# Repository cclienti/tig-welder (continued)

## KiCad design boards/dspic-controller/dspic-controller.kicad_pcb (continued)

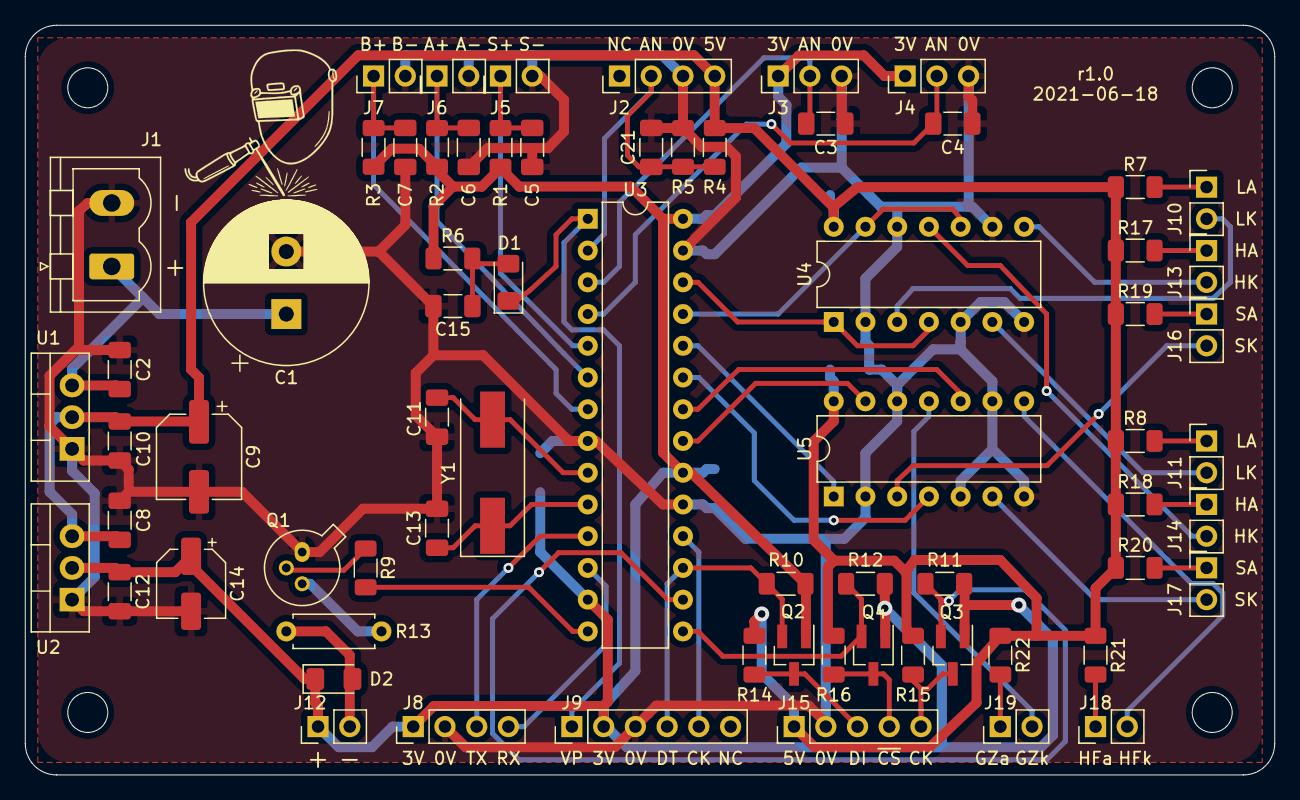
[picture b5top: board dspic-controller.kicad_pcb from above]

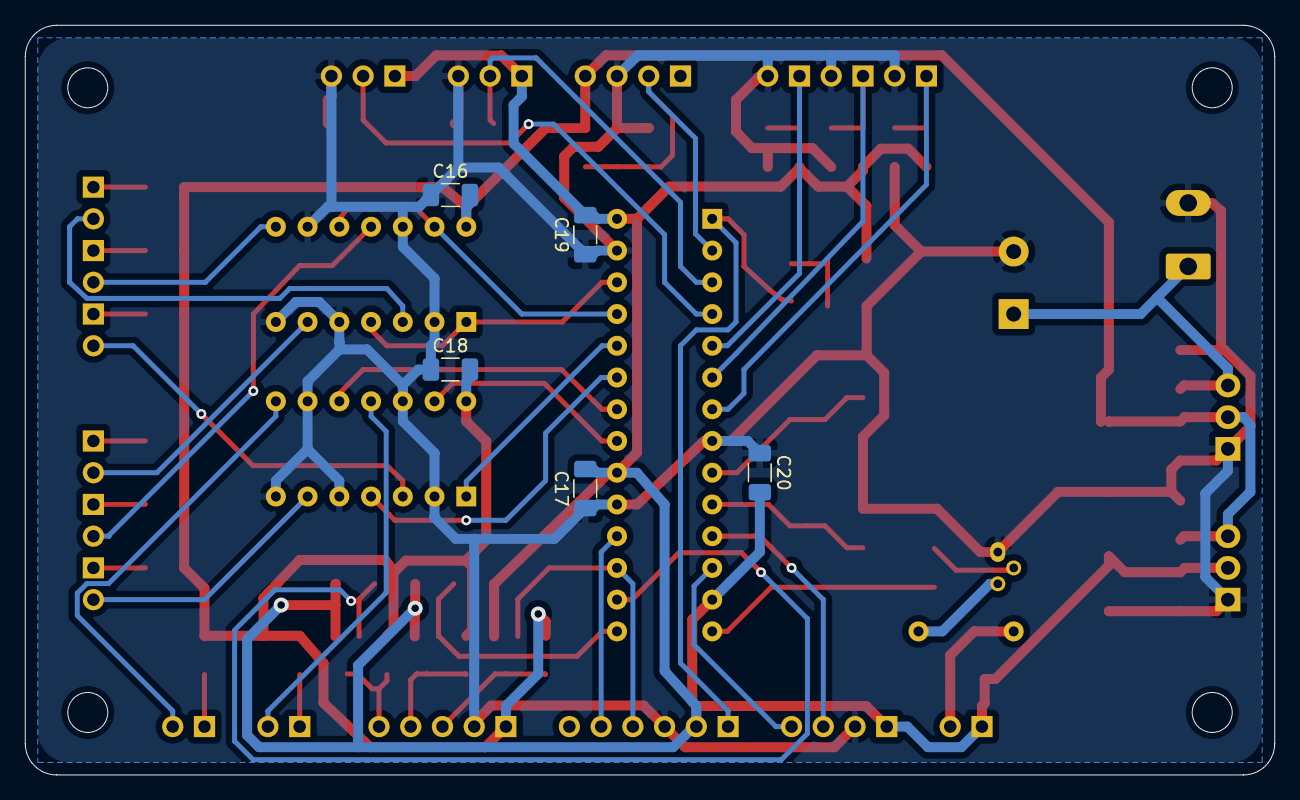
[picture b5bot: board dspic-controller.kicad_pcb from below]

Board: 2 copper layers, 100.0 x 60.0 mm, 78 parts (5 on the bottom side), 49 nets.

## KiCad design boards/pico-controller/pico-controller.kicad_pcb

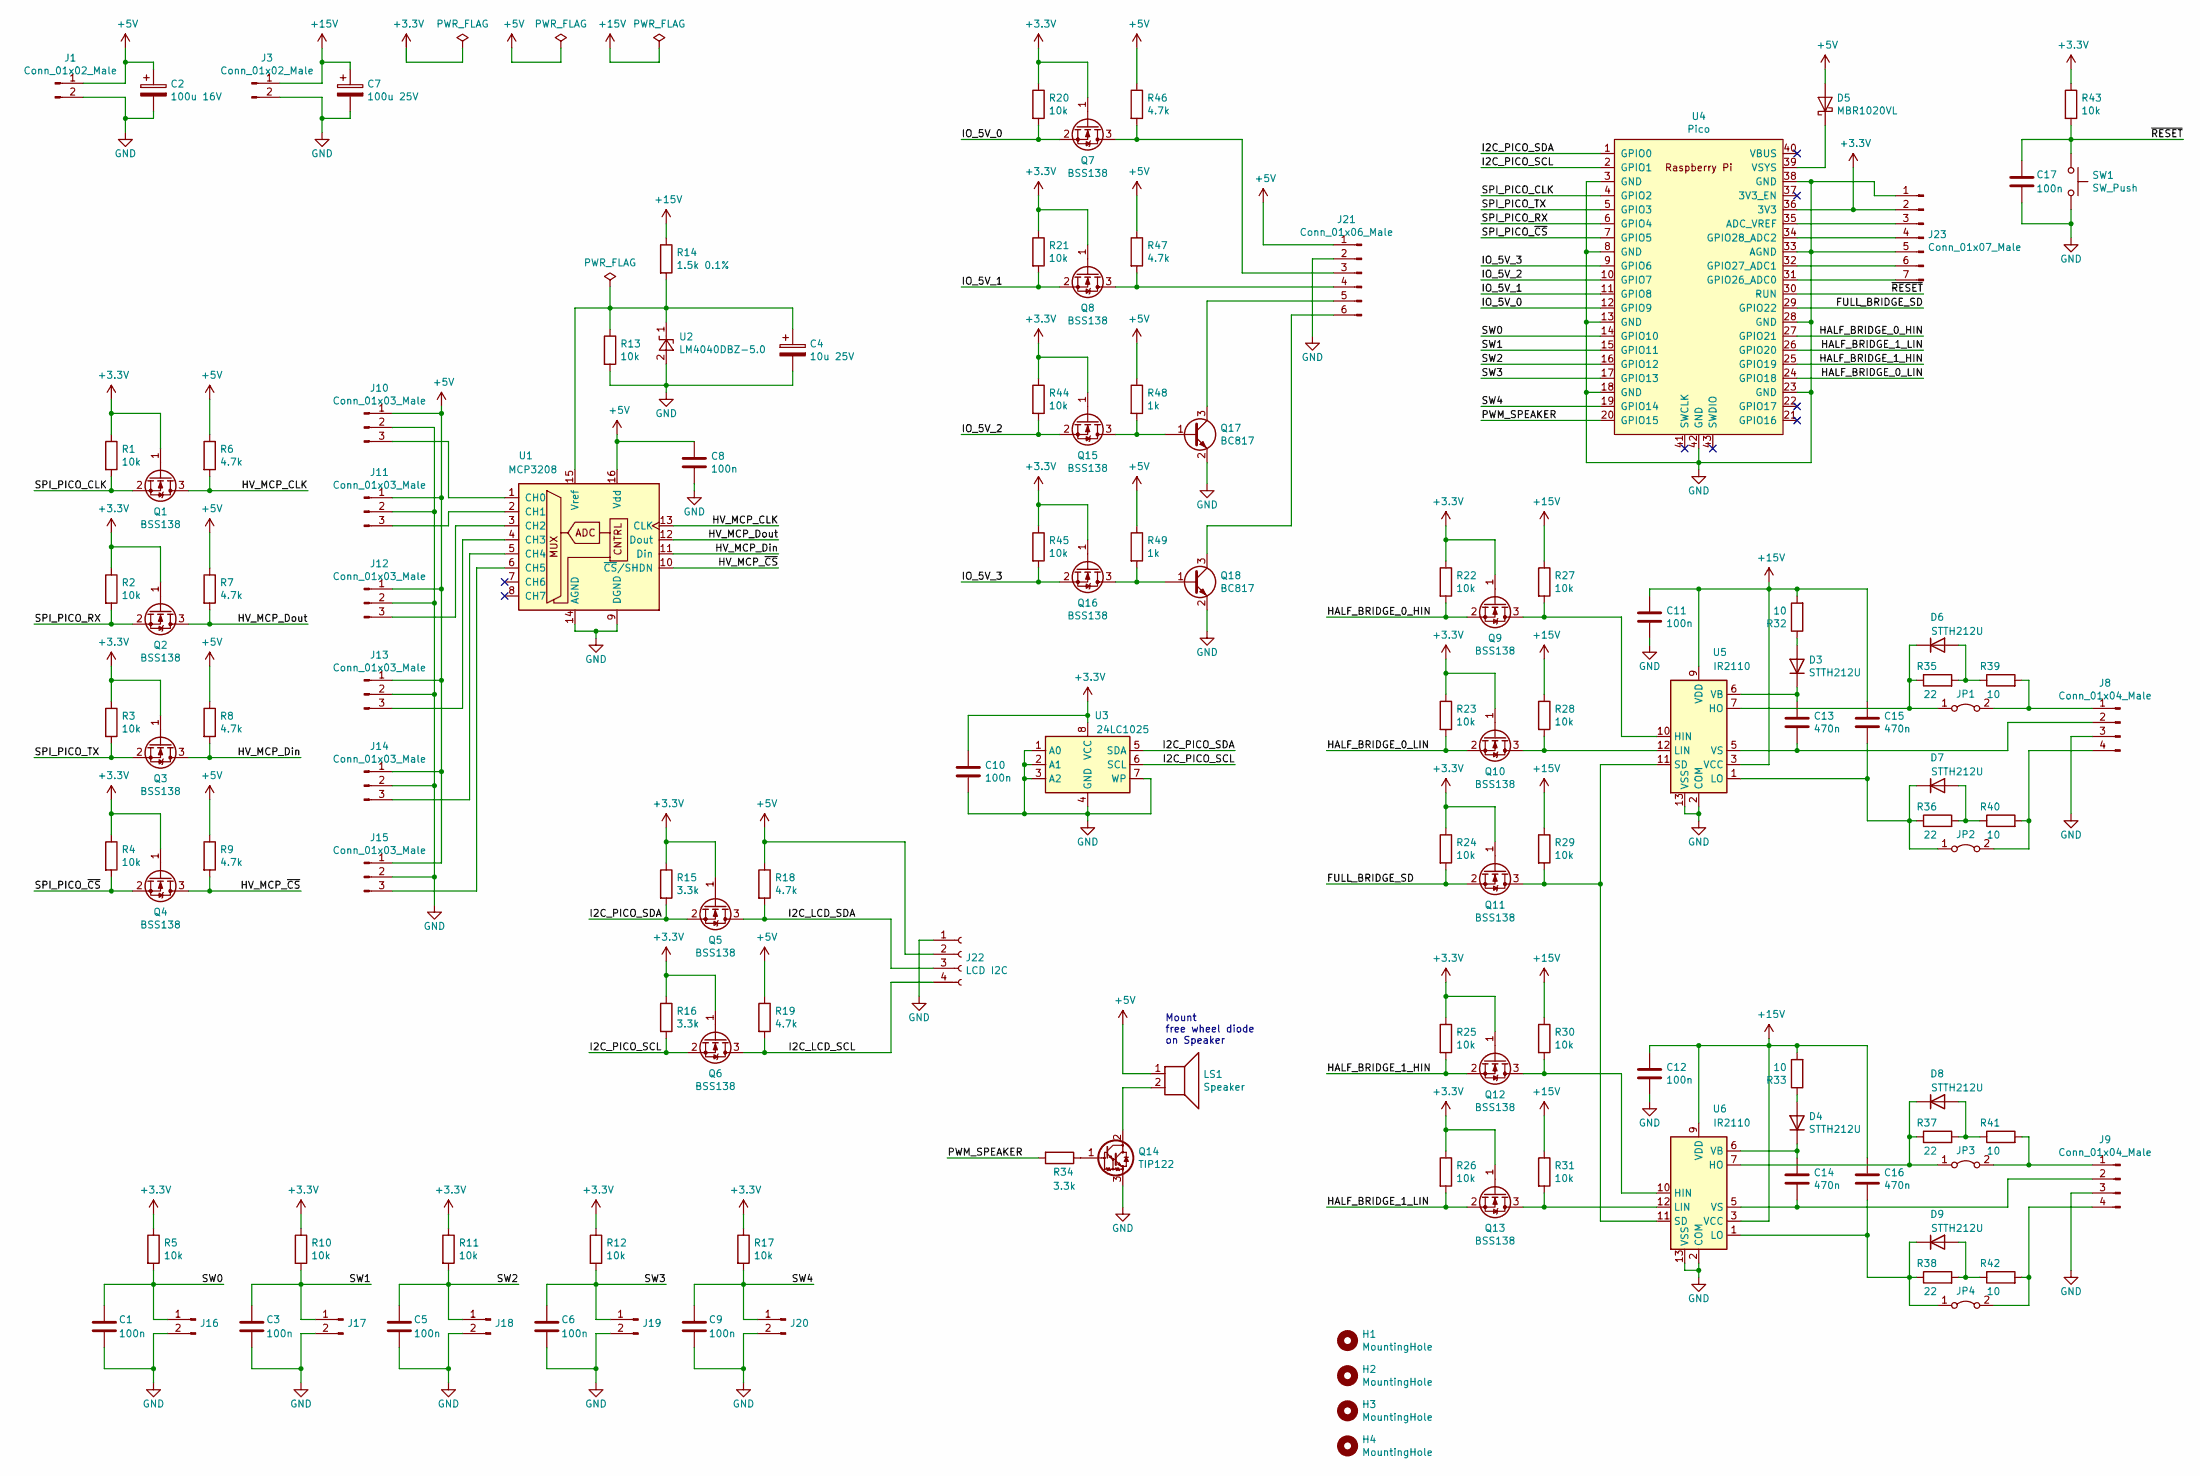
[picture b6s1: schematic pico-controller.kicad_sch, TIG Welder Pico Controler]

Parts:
C1, C3, C5, C6, C8, C9, C10, C11, C12, C17: 100n; C_1206_3216Metric_Pad1.33x1.80mm_HandSolder
C2: 100u 16V; CP_Elec_6.3x5.4
C4: 10u 25V; CP_Elec_5x5.3
C7: 100u 25V; CP_Elec_6.3x7.7
C13, C14, C15, C16: 470n; C_Rect_L13.0mm_W6.0mm_P10.00mm_FKS3_FKP3_MKS4
D3, D4, D6, D7, D8, D9: STTH212U; D_SMB
D5: MBR1020VL; D_SMA
H1, H2, H3, H4: MountingHole; MountingHole_3mm
J1, J3: Conn_01x02_Male; PhoenixContact_MSTBVA_2,5_2-G-5,08_1x02_P5.08mm_Vertical
J8, J9: Conn_01x04_Male; PinHeader_1x04_P2.54mm_Vertical
J10, J11, J12, J13, J14, J15: Conn_01x03_Male; PinHeader_1x03_P2.54mm_Vertical
J16, J17, J18, J19, J20: Conn_01x02_Male; PinHeader_1x02_P2.54mm_Vertical
J21: Conn_01x06_Male; PinHeader_1x06_P2.54mm_Vertical
J22: LCD I2C; PinHeader_1x04_P2.54mm_Vertical
J23: Conn_01x07_Male; PinHeader_1x07_P2.54mm_Vertical
JP1, JP2, JP3, JP4: Jumper_2_Bridged; PinHeader_1x02_P2.54mm_Vertical
LS1: Speaker; PinHeader_1x02_P2.54mm_Vertical
Q1, Q2, Q3, Q4, Q5, Q6, Q7, Q8, Q9, Q10, Q11, Q12, Q13, Q15, Q16: BSS138; SOT-23_Handsoldering
Q14: TIP122; TO-220-3_Horizontal_TabDown
Q17, Q18: BC817; SOT-23
R1, R2, R3, R4, R5, R10, R11, R12, R13, R17, R20, R21, R22, R23, R24, R25, R26, R27, R28, R29, R30, R31, R43, R44, R45: 10k; R_1206_3216Metric_Pad1.30x1.75mm_HandSolder
R6, R7, R8, R9, R18, R19, R46, R47: 4.7k; R_1206_3216Metric_Pad1.30x1.75mm_HandSolder
R14: 1.5k 0.1%; R_1206_3216Metric_Pad1.30x1.75mm_HandSolder
R15, R16, R34: 3.3k; R_1206_3216Metric_Pad1.30x1.75mm_HandSolder
R32, R33, R39, R40, R41, R42: 10; R_1206_3216Metric_Pad1.30x1.75mm_HandSolder
R35, R36, R37, R38: 22; R_1206_3216Metric_Pad1.30x1.75mm_HandSolder
R48, R49: 1k; R_1206_3216Metric_Pad1.30x1.75mm_HandSolder
SW1: SW_Push; SW_PUSH_6mm_H5mm
U1: MCP3208; DIP-16_W7.62mm
U2: LM4040DBZ-5.0; SOT-23_Handsoldering
U3: 24LC1025; DIP-8_W7.62mm
U4: Pico; RPi_Pico_SMD_TH
U5, U6: IR2110; DIP-14_W7.62mm

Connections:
+3V3: C10.1, J23.2, Q1.1 (G), Q2.1 (G), Q3.1 (G), Q4.1 (G), Q5.1 (G), Q6.1 (G), Q7.1 (G), Q8.1 (G), Q9.1 (G), Q10.1 (G), Q11.1 (G), Q12.1 (G), Q13.1 (G), Q15.1 (G), Q16.1 (G), R1.1, R2.1, R3.1, R4.1, R5.1, R10.1, R11.1, R12.1, R15.1, R16.1, R17.1, R20.1, R21.1, R22.1, R23.1, R24.1, R25.1, R26.1, R43.1, R44.1, R45.1, U3.8 (VCC), U4.36 (3V3)
+5V: C2.1, C8.1, D5.2 (A), J1.1, J10.1, J11.1, J12.1, J13.1, J14.1, J15.1, J21.1, J22.2, LS1.1, R6.1, R7.1, R8.1, R9.1, R18.1, R19.1, R46.1, R47.1, R48.1, R49.1, U1.16 (Vdd)
+15V: C7.1, C11.1, C12.1, C15.1, C16.1, J3.1, R14.1, R27.1, R28.1, R29.1, R30.1, R31.1, R32.2, R33.2, U5.3 (VCC), U5.9 (VDD), U6.3 (VCC), U6.9 (VDD)
/FULL_BRIDGE_SD: Q11.2 (S), R24.2, U4.29 (GPIO22)
/HALF_BRIDGE_0_HIN: Q9.2 (S), R22.2, U4.27 (GPIO21)
/HALF_BRIDGE_0_LIN: Q10.2 (S), R23.2, U4.24 (GPIO18)
/HALF_BRIDGE_1_HIN: Q12.2 (S), R25.2, U4.25 (GPIO19)
/HALF_BRIDGE_1_LIN: Q13.2 (S), R26.2, U4.26 (GPIO20)
/HV_MCP_CLK: Q1.3 (D), R6.2, U1.13 (CLK)
/HV_MCP_Din: Q3.3 (D), R8.2, U1.11 (Din)
/HV_MCP_Dout: Q2.3 (D), R7.2, U1.12 (Dout)
/HV_MCP_~CS: Q4.3 (D), R9.2, U1.10 (~CS/SHDN)
/I2C_LCD_SCL: J22.4, Q6.3 (D), R19.2
/I2C_LCD_SDA: J22.3, Q5.3 (D), R18.2
/I2C_PICO_SCL: Q6.2 (S), R16.2, U3.6 (SCL), U4.2 (GPIO1)
/I2C_PICO_SDA: Q5.2 (S), R15.2, U3.5 (SDA), U4.1 (GPIO0)
/IO_5V_0: Q7.2 (S), R20.2, U4.12 (GPIO9)
/IO_5V_1: Q8.2 (S), R21.2, U4.11 (GPIO8)
/IO_5V_2: Q15.2 (S), R44.2, U4.10 (GPIO7)
/IO_5V_3: Q16.2 (S), R45.2, U4.9 (GPIO6)
/PWM_SPEAKER: R34.2, U4.20 (GPIO15)
/SPI_PICO_CLK: Q1.2 (S), R1.2, U4.4 (GPIO2)
/SPI_PICO_RX: Q2.2 (S), R2.2, U4.6 (GPIO4)
/SPI_PICO_TX: Q3.2 (S), R3.2, U4.5 (GPIO3)
/SPI_PICO_~CS: Q4.2 (S), R4.2, U4.7 (GPIO5)
/SW0: C1.1, J16.1, R5.2, U4.14 (GPIO10)
/SW1: C3.1, J17.1, R10.2, U4.15 (GPIO11)
/SW2: C5.1, J18.1, R11.2, U4.16 (GPIO12)
/SW3: C6.1, J19.1, R12.2, U4.17 (GPIO13)
/SW4: C9.1, J20.1, R17.2, U4.19 (GPIO14)
/~RESET: C17.1, R43.2, SW1.1, U4.30 (RUN)
GND: C1.2, C2.2, C3.2, C4.2, C5.2, C6.2, C7.2, C8.2, C9.2, C10.2, C11.2, C12.2, C17.2, J1.2, J3.2, J8.3, J9.3, J10.2, J11.2, J12.2, J13.2, J14.2, J15.2, J16.2, J17.2, J18.2, J19.2, J20.2, J21.2, J22.1, J23.1, J23.5, Q14.3 (E), Q17.2 (E), Q18.2 (E), R13.2, SW1.2, U1.9 (DGND), U1.14 (AGND), U2.2 (A), U3.1 (A0), U3.2 (A1), U3.3 (A2), U3.4 (GND), U3.7 (WP), U4.3 (GND), U4.8 (GND), U4.13 (GND), U4.18 (GND), U4.23 (GND), U4.28 (GND), U4.33 (AGND), U4.38 (GND), U4.42 (GND), U5.2 (COM), U5.13 (VSS), U6.2 (COM), U6.13 (VSS)
unnamed: C4.1, R13.1, R14.2, U1.15 (Vref), U2.1 (K)
unnamed: C13.1, D3.1 (K), U5.6 (VB)
unnamed: C13.2, J8.2, U5.5 (VS)
unnamed: C14.1, D4.1 (K), U6.6 (VB)
unnamed: C14.2, J9.2, U6.5 (VS)
unnamed: C15.2, D7.1 (K), JP2.1 (A), R36.1, U5.1 (LO)
unnamed: C16.2, D9.1 (K), JP4.1 (A), R38.1, U6.1 (LO)
unnamed: D3.2 (A), R32.1
unnamed: D4.2 (A), R33.1
unnamed: D5.1 (K), U4.39 (VSYS)
unnamed: D6.1 (K), JP1.1 (A), R35.1, U5.7 (HO)
unnamed: D6.2 (A), R35.2, R39.1
unnamed: D7.2 (A), R36.2, R40.1
unnamed: D8.1 (K), JP3.1 (A), R37.1, U6.7 (HO)
unnamed: D8.2 (A), R37.2, R41.1
unnamed: D9.2 (A), R38.2, R42.1
unnamed: J8.1, JP1.2 (B), R39.2
unnamed: J8.4, JP2.2 (B), R40.2
unnamed: J9.1, JP3.2 (B), R41.2
unnamed: J9.4, JP4.2 (B), R42.2
unnamed: J10.3, U1.1 (CH0)
unnamed: J11.3, U1.2 (CH1)
unnamed: J12.3, U1.3 (CH2)
unnamed: J13.3, U1.4 (CH3)
unnamed: J14.3, U1.5 (CH4)
unnamed: J15.3, U1.6 (CH5)
unnamed: J21.3, Q7.3 (D), R46.2
unnamed: J21.4, Q8.3 (D), R47.2
unnamed: J21.5, Q17.3 (C)
unnamed: J21.6, Q18.3 (C)
unnamed: J23.3, U4.35 (ADC_VREF)
unnamed: J23.4, U4.34 (GPIO28_ADC2)
unnamed: J23.6, U4.32 (GPIO27_ADC1)
unnamed: J23.7, U4.31 (GPIO26_ADC0)
unnamed: LS1.2, Q14.2 (C)
unnamed: Q9.3 (D), R27.2, U5.10 (HIN)
unnamed: Q10.3 (D), R28.2, U5.12 (LIN)
unnamed: Q11.3 (D), R29.2, U5.11 (SD), U6.11 (SD)
unnamed: Q12.3 (D), R30.2, U6.10 (HIN)
unnamed: Q13.3 (D), R31.2, U6.12 (LIN)
unnamed: Q14.1 (B), R34.1
unnamed: Q15.3 (D), Q17.1 (B), R48.2
unnamed: Q16.3 (D), Q18.1 (B), R49.2

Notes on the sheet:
Mount free wheel diode on Speaker

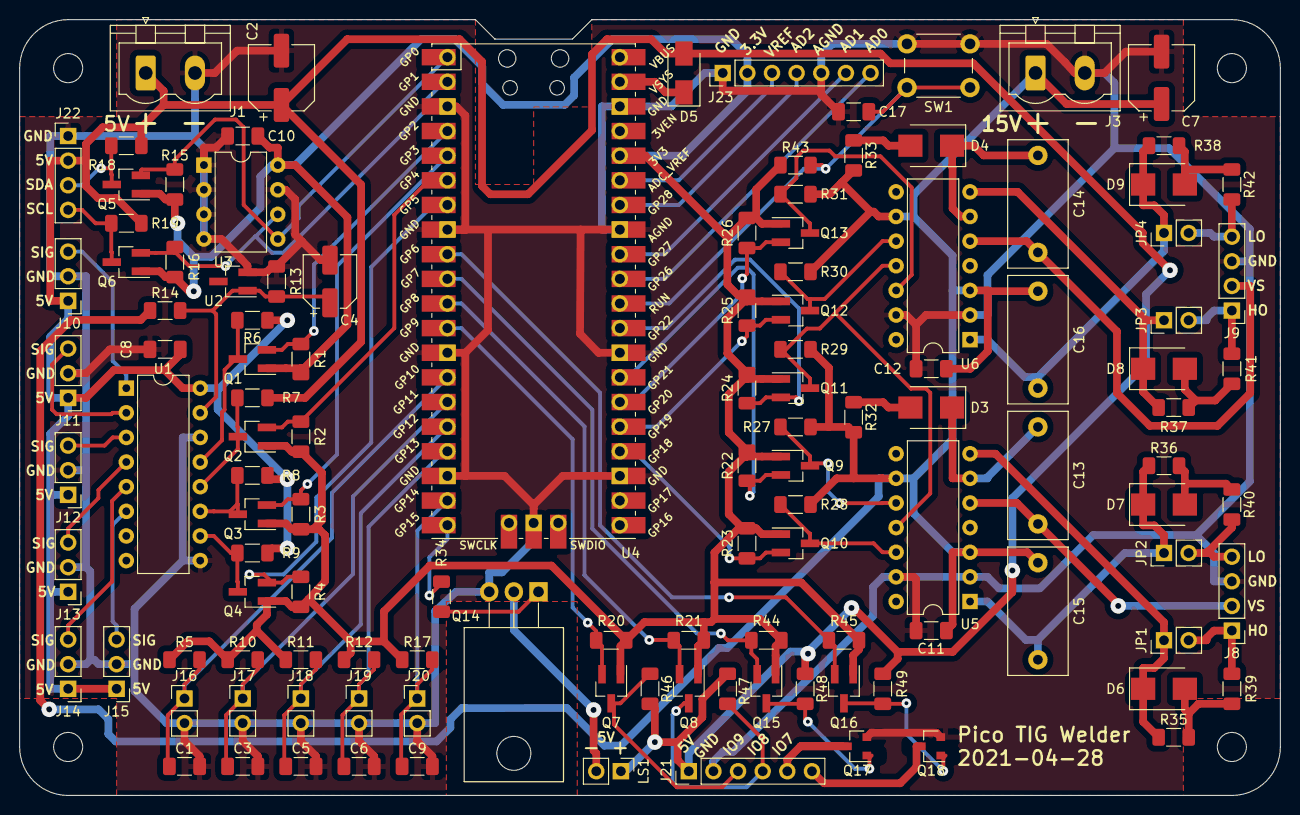
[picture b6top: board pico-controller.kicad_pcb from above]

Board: 2 copper layers, 130.0 x 80.0 mm, 125 parts (0 on the bottom side), 75 nets.

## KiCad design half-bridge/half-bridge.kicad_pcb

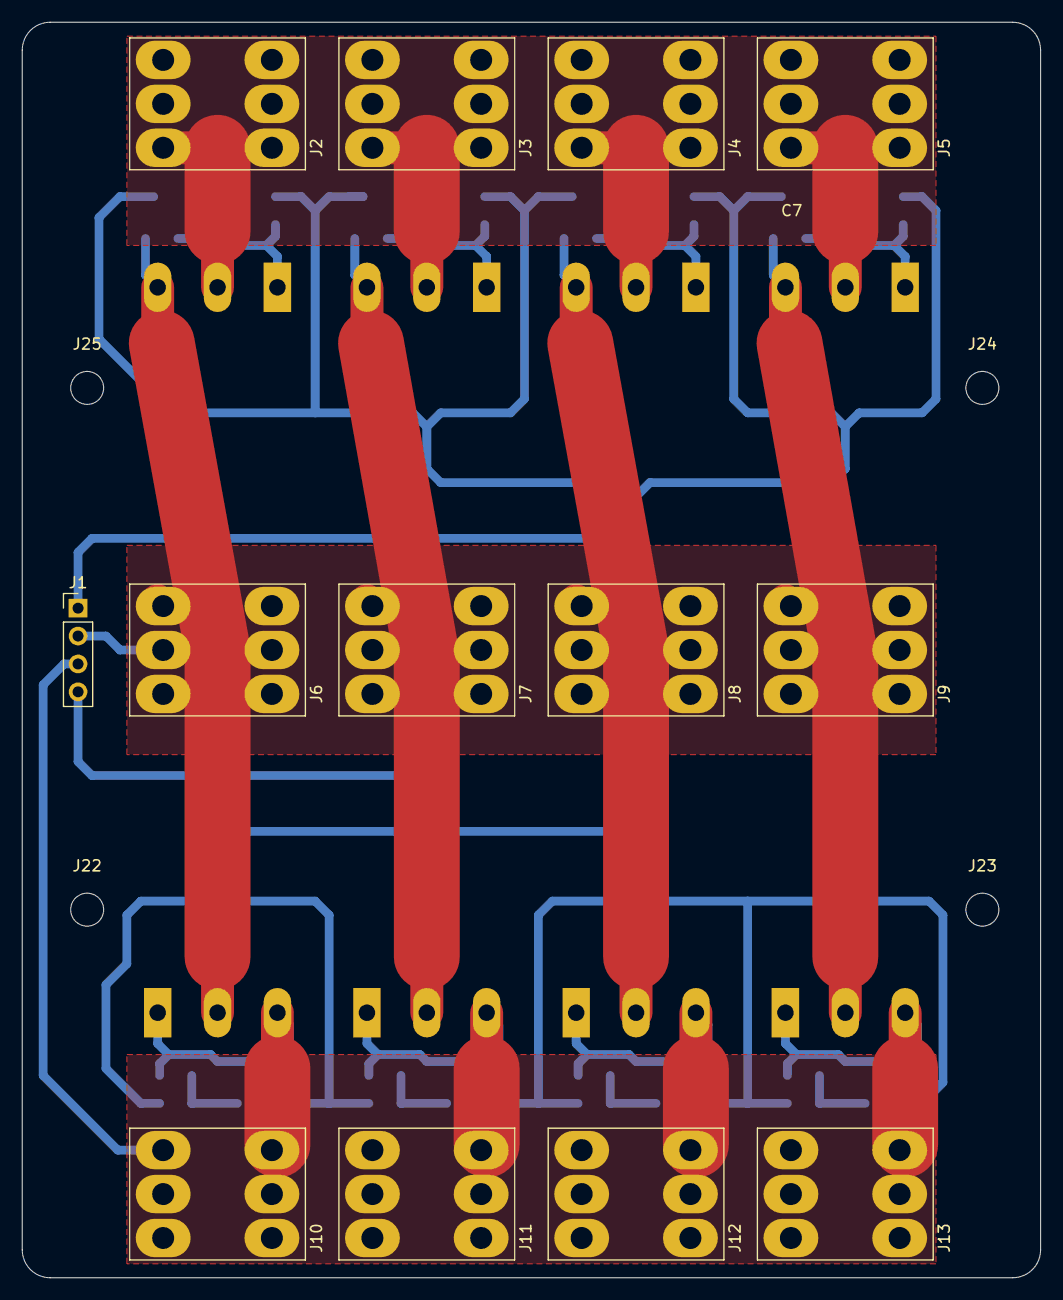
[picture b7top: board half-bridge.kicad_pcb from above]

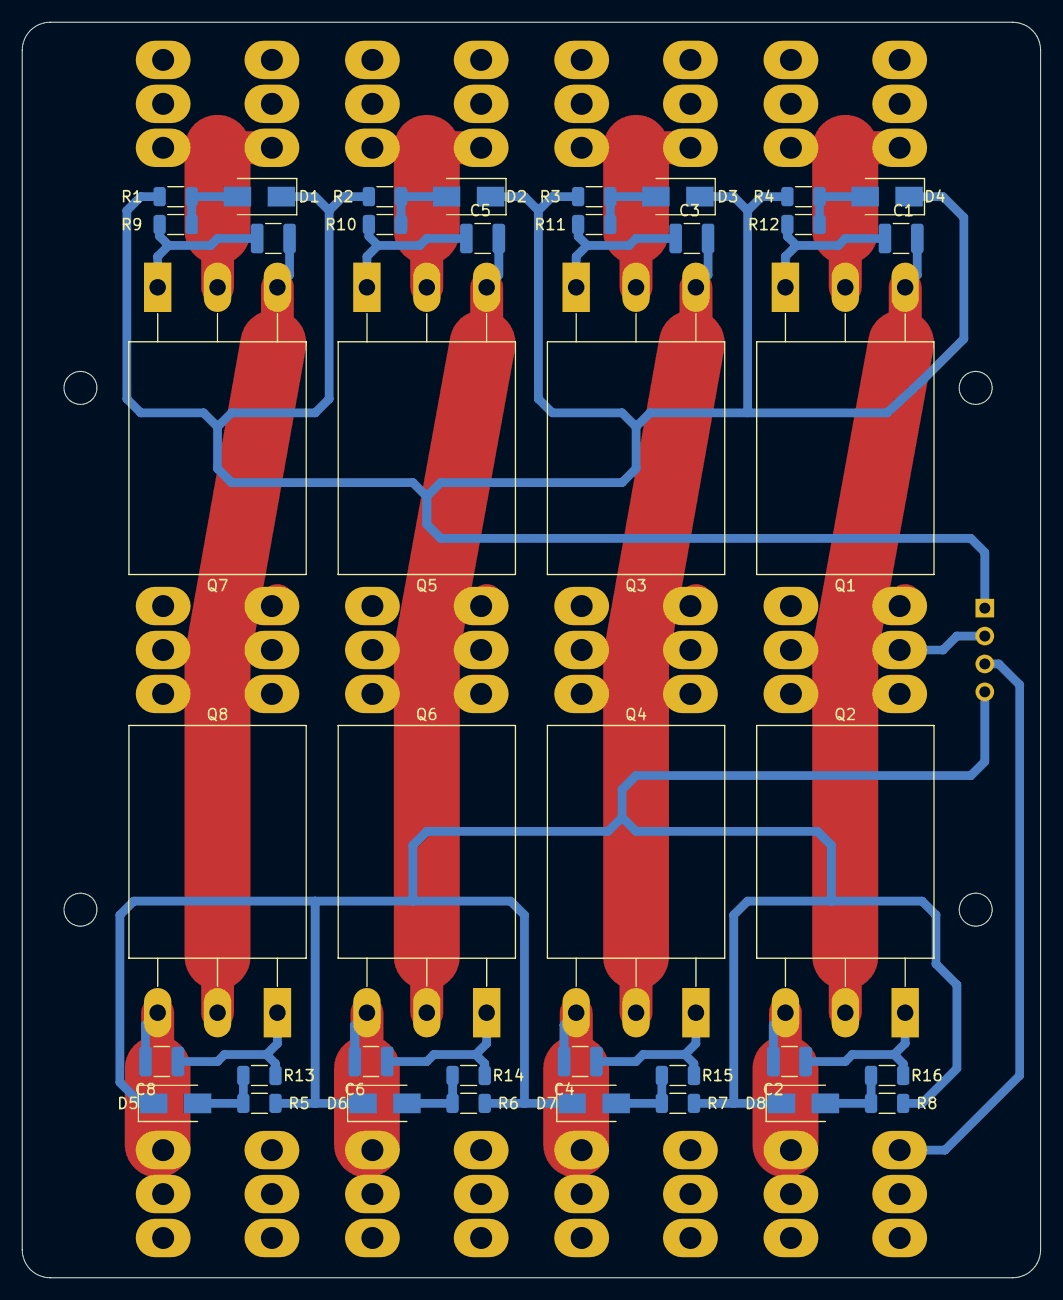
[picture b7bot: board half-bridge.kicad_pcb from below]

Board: 2 copper layers, 92.7 x 114.3 mm, 57 parts (40 on the bottom side), 21 nets.

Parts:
C1, C2, C3, C4, C5, C6, C7, C8: 1n; C_1210_3225Metric
D1, D2, D3, D4, D5, D6, D7, D8: 1N4005; D_SMA
J1: Conn_01x04_Male; PinHeader_1x04_P2.54mm_Vertical
J2, J3, J4, J5, J6, J7, J8, J9, J10, J11, J12, J13: Conn_01x01_Female; Terminal_Block_Welder_no_hole
J22, J23, J24, J25: Conn_01x01_Female; MountingHole_3mm
Q1, Q2, Q3, Q4, Q5, Q6, Q7, Q8: Q_NIGBT_GCE; TO-247-3_Horizontal_TabUp
R1, R2, R3, R4, R5, R6, R7, R8: 22; R_1206_3216Metric
R9, R10, R11, R12, R13, R14, R15, R16: 10; R_1206_3216Metric

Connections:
/GND: C2.2, C4.2, C6.2, C8.2, J1.3, J10.1, J11.1, J12.1, J13.1, Q2.3, Q4.3, Q6.3, Q8.3
/VCC: J2.1, J3.1, J4.1, J5.1, Q1.2, Q3.2, Q5.2, Q7.2
unnamed: C1.1, Q1.1, R12.2
unnamed: C1.2, C3.2, C5.2, C7.2, J1.2, J6.1, J7.1, J8.1, J9.1, Q1.3, Q2.2, Q3.3, Q4.2, Q5.3, Q6.2, Q7.3, Q8.2
unnamed: C2.1, Q2.1, R16.2
unnamed: C3.1, Q3.1, R11.2
unnamed: C4.1, Q4.1, R15.2
unnamed: C5.1, Q5.1, R10.2
unnamed: C6.1, Q6.1, R14.2
unnamed: C7.1, Q7.1, R9.2
unnamed: C8.1, Q8.1, R13.2
unnamed: D1.1, D2.1, D3.1, D4.1, J1.1, R1.1, R2.1, R3.1, R4.1
unnamed: D1.2, R1.2, R9.1
unnamed: D2.2, R2.2, R10.1
unnamed: D3.2, R3.2, R11.1
unnamed: D4.2, R4.2, R12.1
unnamed: D5.1, D6.1, D7.1, D8.1, J1.4, R5.1, R6.1, R7.1, R8.1
unnamed: D5.2, R5.2, R13.1
unnamed: D6.2, R6.2, R14.1
unnamed: D7.2, R7.2, R15.1
unnamed: D8.2, R8.2, R16.1

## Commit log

2021-05-13 Initial commit of schedmatic and pcb files
2021-05-13 Moved schematics and PCB to a dedicated root dir
2021-05-13 Added the lcd_display class to control the LCD 4x20
2021-05-13 Added the GPL-V3 license header
2021-05-13 Moving to git submodules for the pico-sdk
2021-05-13 Reduced volatage of the speaker in the tig-welder controller board
2021-05-13 Added gdb init script for picoprobe
2021-05-13 Fixed CMakeLists.txt to use the pico SDK as a submodule
2021-05-13 Added a notebook to generate the LUT for the thermistance CTN
    The CTN is used by the tig-welder controller board to monitor the
    H-Bridge temperature during welding.
2021-05-13 Added firmware template project
2021-05-13 Switched LCDDisplay to a basic but efficient printf method
2021-05-13 Added the README.md template
2021-05-13 Added a script to build the picoprobe and the openocd of the pi pico
2021-05-13 Added support for the buzzer in the firmware of the controller
2021-05-13 Updated git ignore to hide some kicad files
2021-05-13 Added the Rotary Encoder (PIO) and the ADC (MCP3208) classes
2021-05-13 Updated gitignore to ignore clang cache dir
2021-05-13 Added Switch and Relay class
2021-05-13 Reworked the half-bridge to be more modular
2021-05-13 Changed branch of the pico-sdk to tag 1.1.2
2021-05-13 Added a script to start openocd for the picoprobe
2021-05-13 Fixed bad parameter order in LCDDisplay ctor
    The num_lines and num_cols were interchanged. Default values for cols
    where apply to lines and vice versa.
2021-05-13 Added methods to LCDDisplay class
2021-05-13 Fixed high power consumption when the buzzer is idle
2021-05-13 Fixed discrepancy between set/get_rotation in RotaryEncoder class
    As the get_rotation divides by four the value to reduce the sensitivity,
    the set_rotation must multiply by four the rotation value that must be
    updated.
2021-05-13 Removed unnecessary statement in lcd_display.cpp
2021-05-13 Added the lcd_menu class in the firmware
2021-05-14 Added mute/unmute capability to the buzzer class
2021-05-14 Fixed float precision display in the LCDMenu class
2021-05-14 Added the possibility to choose the title and value LCD row index
2021-05-14 Removed forward declaration in the LCDMenu class
2021-05-14 Manage menu default value at the registration step
    The variable tracked by the menu can be not correctly initialized. By
    using the get/set_value from the menu entry class, we ensure that the
    value tracked is legal.
2021-05-14 Reworked the main process to enable buzzer mute/unmute
2021-05-14 Added Splash info display in LCDMenu class
2021-05-14 Fixed issues with the MenuEntryInt (bad unit and bad cast)
2021-05-14 Added a struct to hold all welding parameters
2021-05-15 Fixed exec right on build-picoprobe.sh script
2021-05-15 Added footer monitoring value in the LCDMenu class
2021-05-15 Reworked menu entry class to simplify the refresh function
2021-05-15 Reworked splash screen display in the LCDMenu class
2021-05-15 Removed space after ":" in LCDMenu footer to save space
2021-05-15 Simplied title construction in LCDMenu entry base class
2021-05-15 Added docs for the LCDMenu methods
2021-05-15 Added support for custom char definition in the LCDDisplay class
2021-05-15 Improved rendering of the LCDMenu
    - Support for custom char to improve Title and Footer area rendering
    - Manage properly the splash screen without clearing the screen every
    time.
2021-05-24 Added a script to flash the pico without a debugger
2021-05-24 Added docs in the notebook to describe the CTN connection
2021-05-24 First version of a welding basic control loop
2021-05-25 Improved the flash script to start screen at the end
2021-06-03 Added functions to average successive ADC reads
2021-06-03 Reworked the warning sound in the buzzer class
2021-06-03 Improved the script to flash the PICO using the serial interface
2021-06-03 Added the HBridge class to manage the four IGBT transistors
2021-06-03 Added a tool to transform fonts into C array initialization
2021-06-03 Moved the pico firmware in a dedicated firmware project
2021-06-03 Added the pic18f2550 firmware for the simple relay welder project
2021-06-03 Cleaned interfaces and added documentation
2021-06-04 Added print methods to display string, int and decimal numbers
2021-06-06 Added mechanical schematics
2021-06-13 Added an opto-isolated mosfet/igbt driver board
2021-06-13 Exchanged the ARC pin with the GAZ pin
2021-06-21 Added the dsPIC30F4012 controller board
2021-07-15 Moved the pic18f project to dspic
2021-07-15 Added the relay board to manage GAZ and HF Spark start
2023-11-25 pico-controller: added the cache lib
2023-11-25 pico-controller: switched to kicad 7
2023-11-25 dspic-controller: updated the project to kicad 7
2023-11-25 half-bridge-mod: updated to kicad 7
2023-11-25 power-driver: updated to kicad 7
2023-11-25 slow-switching-outputs: updated to kicad 7
2023-11-25 small-power: updated to kicad 7
